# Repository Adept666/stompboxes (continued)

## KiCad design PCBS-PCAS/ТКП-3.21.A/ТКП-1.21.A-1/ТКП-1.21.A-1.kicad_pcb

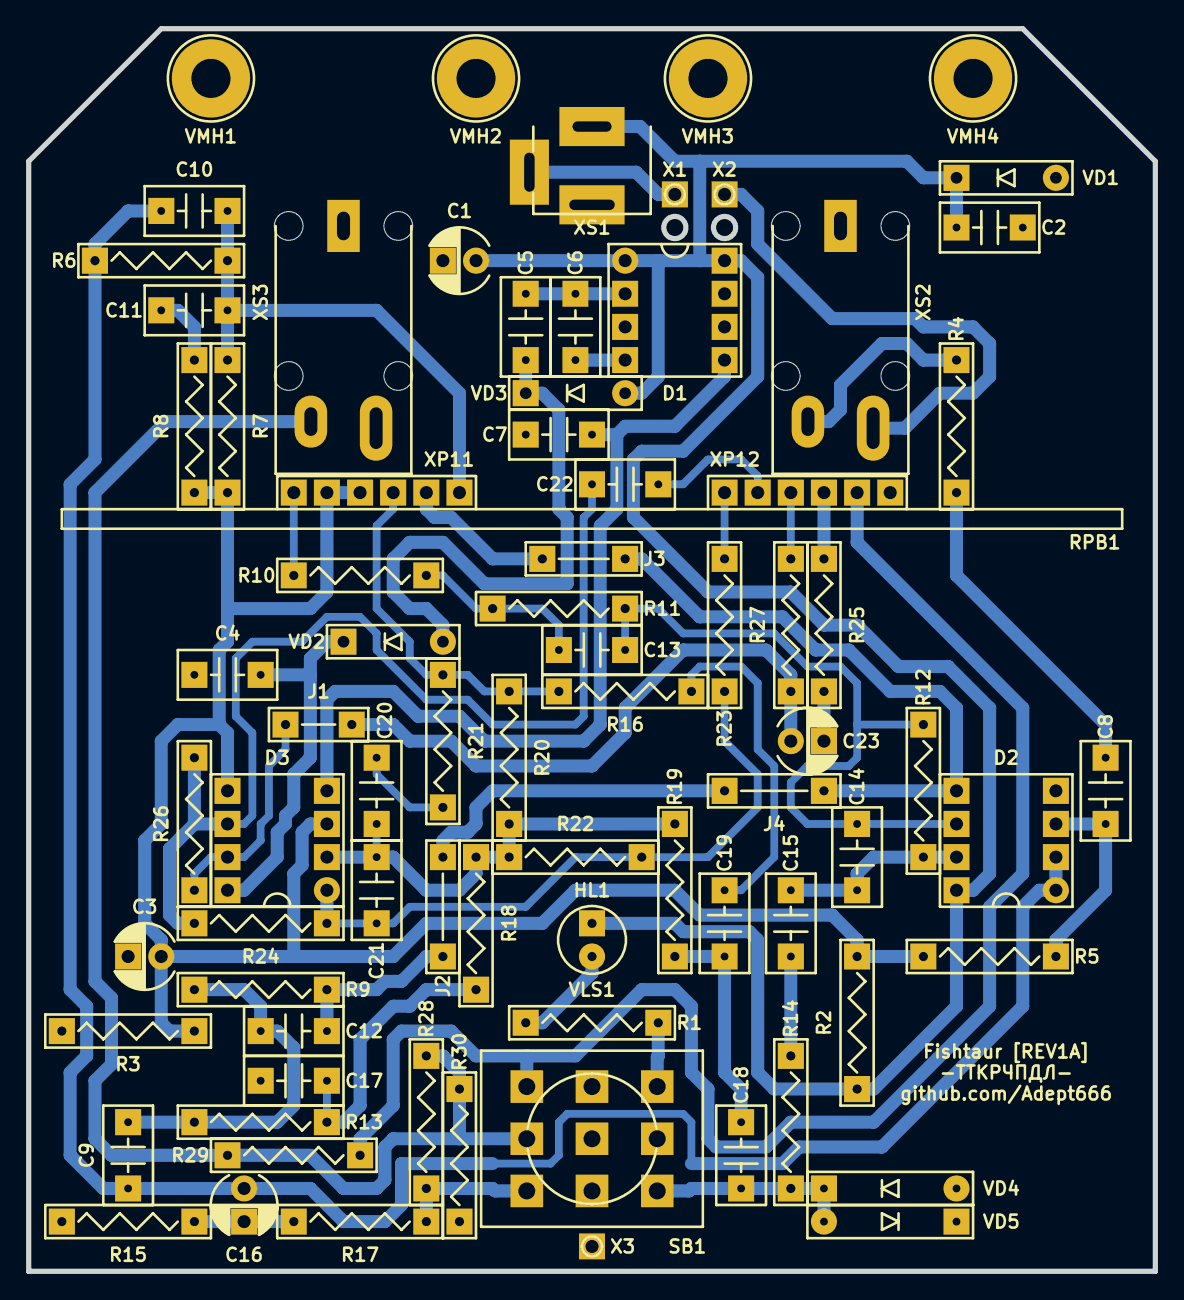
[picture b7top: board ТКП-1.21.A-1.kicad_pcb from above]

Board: 2 copper layers, 86.4 x 95.3 mm, 81 parts (0 on the bottom side), 44 nets.

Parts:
C1, C3: 476; CP-RADIAL-D05.0-P02.0-CLS
C2, C8, C9: 104; C-DISK-D04.2-T03.0-P05.08-d0.5
C4, C5, C6, C7, C15, C17, C18: 105; C-DISK-D04.2-T03.0-P05.08-d0.5
C10, C12: 683; C-DISK-D04.2-T03.0-P05.08-d0.5
C11: 334; C-DISK-D04.2-T03.0-P05.08-d0.5
C13: 823; C-DISK-D04.2-T03.0-P05.08-d0.5
C14: 391; C-DISK-D04.2-T03.0-P05.08-d0.5
C16, C23: 475; CP-RADIAL-D05.0-P02.0-CLS
C19: 222; C-DISK-D04.2-T03.0-P05.08-d0.5
C20: 223; C-DISK-D04.2-T03.0-P05.08-d0.5
C21: 821; C-DISK-D04.2-T03.0-P05.08-d0.5
C22: 392; C-DISK-D04.2-T03.0-P05.08-d0.5
D1: 7660S; P-DIP-08
D2, D3: 072; P-DIP-08
GB1: PP3; B-PP3-HV
HL1: FYL-5013UWC; LED-ROUND-05.0-UNI-SH-SPACER-PNL-5.3
J1: 0.6; J-TH-d0.6-P05.08
J2, J4: 0.6; J-TH-d0.6-P07.62
J3: 0.6; J-TH-d0.6-P06.35
R1, R4, R9: 103; R-MFR-25
R2, R3, R20: 273; R-MFR-25
R5: 105; R-MFR-25
R6: 512; R-MFR-25
R7, R13: 152; R-MFR-25
R8, R14: 102; R-MFR-25
R10: 202; R-MFR-25
R11, R18: 153; R-MFR-25
R12: 434; R-MFR-25
R15, R24, R26, R30: 104; R-MFR-25
R16: 223; R-MFR-25
R17, R25: 561; R-MFR-25
R19: 473; R-MFR-25
R21: 123; R-MFR-25
R22: 394; R-MFR-25
R23: 182; R-MFR-25
R27: 472; R-MFR-25
R28, R29: 683; R-MFR-25
RPB1: B100K-B10K-B10K; RPB-1590BB-18-3x17-DUAL-SINGLE-SINGLE-1.5-PNL-7.4-2.8
SB1: PBS-24-302SP; SW-PBS-24-302SP-2.5-PNL-13.0
VD1: 4742A; P-DO-41
VD2, VD3: 4001; P-DO-41
VD4, VD5: Д9Б; P-DO-7
VE1: 1590BB; 1590BB_B1
VLS1: BR-12.7; VLS-BR
VMH1, VMH2, VMH3, VMH4: DI5M3x18; VMH-STA-DA5-PNL-3.0
X1: +; CON-PAD-S-1.0-2.0
X2: -; CON-PAD-S-1.0-2.0
X3: COM; CON-PAD-S-1.0-2.0
XS1: DC-005; CON-DC-005
XS2: ST-008S-04; CON-ST-008X-04-OR-ST-008X-05
XS3: ST-008S-05; CON-ST-008X-04-OR-ST-008X-05

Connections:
/BYPASS: R17.2, R28.1, SB1.NC1
/EFFECT: R29.1, RPB1.32, SB1.NO1
/IN: R4.1, XS2.T
/J1: C23.+, D3.7, J1.J, R26.2, R27.2
/J2: C12.2, D2.5, J2.J, J3.J, J4.J, R9.2, RPB1.11
/LED: R1.1, SB1.NO3
/LED-CIR: C18.1, R14.2, SB1.NC3, VD4.C, VD5.A
/OUT: R28.2, R29.2, R30.2, SB1.COM1, XS3.T
/PP3-NEG: X2.1, XS2.R/TN
/PP3-POS: X1.1, XS1.SN
COM: C1.-, C2.2, C3.-, C4.2, C7.1, C17.2, D1.3, D2.4, R3.1, R15.1, R30.1, RPB1.31, SB1.COM2, SB1.COM3, SB1.NC2, VD1.A, VD4.A, VD5.C, VMH1.0, VMH2.0, VMH3.0, VMH4.0, X3.1, XS1.C, XS2.S, XS3.S
unnamed: C5.1, VD2.A, VD3.C
unnamed: C5.2, C6.1, D1.2
unnamed: C6.2, D1.4
unnamed: C8.1, R4.2
unnamed: C8.2, D2.3, R5.2
unnamed: C9.1, C10.1, C16.+, D2.1, D2.2, R6.2
unnamed: C10.2, C11.1, R6.1, R7.2, RPB1.14
unnamed: C11.2, R8.2
unnamed: C9.2, C12.1, R9.1, R13.1
unnamed: C13.1, R10.1, R11.1
unnamed: C13.2, C14.1, D2.6, R11.2, R12.1
unnamed: C14.2, C15.1, D2.7, R12.2
unnamed: C15.2, R14.1
unnamed: C16.-, R15.2, R17.1
unnamed: C17.1, R13.2, R18.1
unnamed: C18.2, C19.1, R19.1
unnamed: C19.2, R16.2
unnamed: C20.1, C21.1, D3.2, R18.2, R19.2, R20.2, R22.1
unnamed: C20.2, R21.2
unnamed: C21.2, D3.1, R22.2, R23.1, R24.1
unnamed: C22.1, RPB1.22
unnamed: C22.2, D3.6, R24.2, R26.1
unnamed: C23.-, R25.1
unnamed: HL1.C, R1.2
unnamed: R10.2, RPB1.13
unnamed: R16.1, R20.1, R21.1, RPB1.15
unnamed: R23.2, RPB1.23
unnamed: R25.2, RPB1.33
unnamed: R27.1, RPB1.21
VA: C1.+, C2.1, D1.1, D1.8, D2.8, HL1.A, R2.2, VD1.C, VD3.A, XS1.S
VB: C4.1, D3.8, VD2.C
VC: C7.2, D1.5, D3.4
VREF: C3.+, D3.3, D3.5, R2.1, R3.2, R5.1, R7.1, R8.1, RPB1.12, RPB1.16

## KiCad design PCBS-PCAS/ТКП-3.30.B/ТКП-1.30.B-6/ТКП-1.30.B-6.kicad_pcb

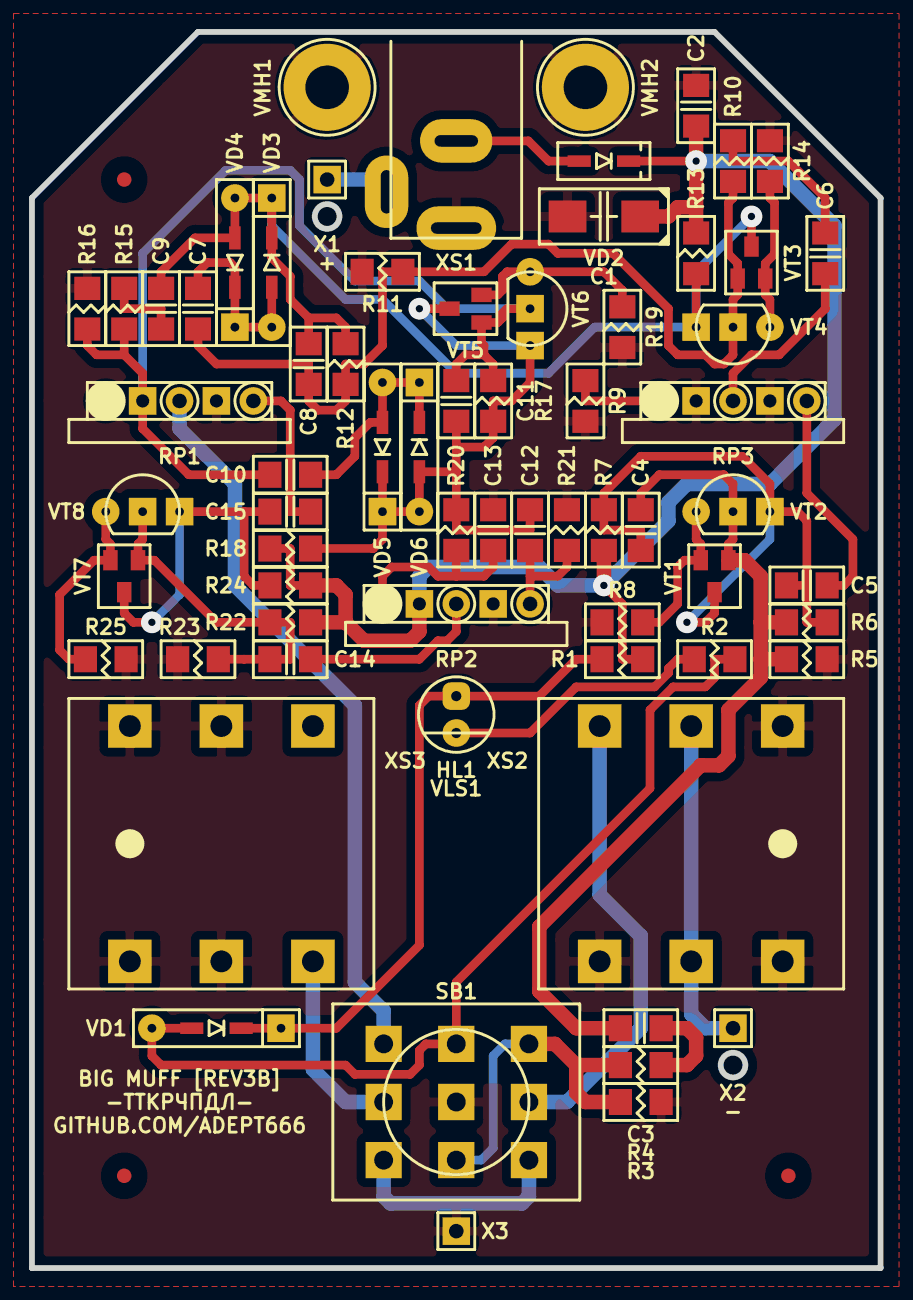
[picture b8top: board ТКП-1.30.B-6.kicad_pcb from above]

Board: 2 copper layers, 58.4 x 85.1 mm, 74 parts (0 on the bottom side), 37 nets.

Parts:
C1: 106; CP-CTSMD-C
C2, C5, C6, C9, C15: 104; C-SM-1206
C3, C14: 105; C-SM-1206
C4, C8, C11: 471; C-SM-1206
C7, C10: 683; C-SM-1206
C12: 332; C-SM-1206
C13: 103; C-SM-1206
GB1: X; B-PP3-HV
HL1: FYL-3014UWC; LED-ROUND-05.0-UNI-SH-SPACER-PNL-5.3
R1: 0; R-SM-1206
R2: 433; R-SM-1206
R3: 105; R-SM-1206
R4: 393; R-SM-1206
R5, R11, R16, R23: 104; R-SM-1206
R6, R12, R17, R22: 474; R-SM-1206
R7, R13, R18: 123; R-SM-1206
R8, R14, R19: 391; R-SM-1206
R9: 102; R-SM-1206
R10, R15, R24: 103; R-SM-1206
R20, R21: 223; R-SM-1206
R25: 272; R-SM-1206
RP1, RP3: A100K; RPB-18-1x17-1.6-PNL-7.2
RP2: B100K; RPB-18-1x17-1.6-PNL-7.2
SB1: PBS-24-302SP; SW-PBS-24-302SP-2.5-PNL-12.0
VD1: X; P-SOD-123-OR-DO-35-V2
VD2: 0520; P-SOD-123
VD3, VD4, VD5, VD6: 4148; P-SOD-123-OR-DO-35-V2
VE1: ТКП-6.3.1.A2.A1.A.1-1; ТКП-6.3.1.A2.A1.A
VE2: ТКП-6.3.3.A1.A1.3-1.A1.00; ТКП-6.3.3.A1
VFM1, VFM2, VFM3: 1.0; VFM-1.0-3.0-SL
VLS1: 2xBR-7.7; VLS-BR-P
VMH1, VMH2: DI5M3x20; VMH-STA-DA5-PNL-3.0
VT1, VT3, VT5, VT7: 847; P-SOT-23-B-E-C
VT2, VT4, VT6, VT8: 547; P-TO-92-E-B-C
X1, X2, X3: X; CON-PAD-S-1.0-1.9
XS1: DC-005; CON-DC-005-9V-OVAL
XS2, XS3: PJ-644C; CON-PJ-644C-IN-OR-OUT

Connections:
/1B: C3.2, C4.1, R5.2, R6.1, VT1.B, VT2.B
/1C: C4.2, C5.1, R6.2, R7.1, VT1.C, VT2.C
/1E: R8.2, VT1.E, VT2.E
/2B: C7.1, C8.1, R10.2, R11.2, R12.1, VT3.B, VT4.B
/2C: C8.2, C9.1, R12.2, R13.1, VD3.C, VD4.A, VT3.C, VT4.C
/2E: R14.2, VT3.E, VT4.E
/3B: C10.1, C11.1, R15.2, R16.2, R17.1, RP1.NC1, VT5.B, VT6.B
/3C: C11.2, C12.1, R17.2, R18.1, R20.1, VD5.C, VD6.A, VT5.C, VT6.C
/3E: R19.2, VT5.E, VT6.E
/4B: C14.2, R22.1, R23.2, VT7.B, VT8.B
/4C: C15.1, R24.1, VT7.C, VT8.C
/4E: R25.2, VT7.E, VT8.E
/IN-CIR: R3.2, R4.1, SB1.NC2, SB1.NO3
/IN-CON: SB1.COM3, XS2.T
/LED: R2.1, SB1.NO2, VD1.A
/OUT-CIR: RP1.2, SB1.NO1
/OUT-CON: SB1.COM1, XS3.T
/PP3-NEG: X2.1, XS2.R, XS2.RN
/PP3-POS: X1.1, XS1.SN
COM: C1.-, C2.2, C13.2, R3.1, R5.1, R8.1, R9.1, R11.1, R14.1, R16.1, R19.1, R21.2, R23.1, R25.1, RP1.1, RP1.NC2, RP2.NC2, RP3.NC1, RP3.NC2, SB1.COM2, VMH1.0, VMH2.0, X3.1, XS1.C, XS2.S, XS2.SN, XS2.TN, XS3.R, XS3.RN, XS3.S, XS3.SN
unnamed: C3.1, R4.2
unnamed: C5.2, RP3.3
unnamed: C6.1, RP3.2
unnamed: C6.2, R10.1
unnamed: C7.2, VD3.A, VD4.C
unnamed: C9.2, R15.1
unnamed: C10.2, VD5.A, VD6.C
unnamed: C12.2, R21.1, RP2.3
unnamed: C13.1, R20.2, RP2.1
unnamed: C14.1, RP2.2
unnamed: C15.2, RP1.3
unnamed: HL1.A, R1.2, VD1.C
unnamed: HL1.C, R2.2
unnamed: R9.2, RP3.1
unnamed: SB1.NC1, SB1.NC3
unnamed: VD2.A, XS1.S
V: C1.+, C2.1, R1.1, R7.2, R13.2, R18.2, R22.2, R24.2, RP2.NC1, VD2.C

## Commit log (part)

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2023-08-25 ТКП-1.23.A-1 Salty Phaser [REV1A]: minor changes
2023-08-25 ТКП-1.37.A Little Angel Chorus [REV2A]: project files are moved to cipher-based storage directory
2023-08-25 Minor changes
2023-09-18 Enclosure parts: ТКП-6.3.2.A1 added
2023-09-19 Enclosure parts: ТКП-6.3.1.A1 modified
2023-09-24 Enclosure parts: draft version of ТКП-6.3.3.A1 added
2023-09-24 Enclosure parts: ТКП-6.3.1.B1 modified
2023-09-24 Enclosure parts: minor changes
2023-10-07 SBKCL: CP-RADIAL-D05.0-P02.0-CLS-OR-D06.3-P02.5-CLS-OR-D08.0-P03.5-CLS footprints modified
2023-10-07 ТКП-1.23.B-1 Salty Phaser [REV1B]: technical requirements added
2023-10-07 ТКП-1.23.B-1 Salty Phaser [REV1B]: TP4…7 added
2023-10-08 ТКП-1.23.B-1 Salty Phaser [REV1B]: PS.VD2 added
2023-10-08 ТКП-1.23.B-1 Salty Phaser [REV1B]: J1, J2, TP8, and TP9 added
2023-10-08 ТКП-1.23.B-1 Salty Phaser [REV1B]: L.R9 added
2023-10-08 ТКП-1.23.B-1 Salty Phaser [REV1B]: L.R10 added
2023-10-09 ТКП-1.23.B-1 Salty Phaser [REV1B]: J6, J7, and L.J1 added
2023-10-15 ТКП-1.23.B-1 Salty Phaser [REV1B]: PS.C6, PS.D1, PS.R3, PS.R4, PS.VD3, and PS.VD4 added
2023-10-25 ТКП-1.23.B-1 Salty Phaser [REV1B]: MS.R9 and MS.R10 added
2023-10-29 ТКП-1.23.B-1 Salty Phaser [REV1B]: TP11 added
2023-10-30 ТКП-1.38.A Phaser A [REV1A]: some changes
2023-10-30 ТКП-1.27.B 1590N1 Connector Board [REV1B]: project files are moved to cipher-based storage directory
2023-11-07 ТКП-1.27.B-1 1590N1 Connector Board [REV1B] A: minor changes
2023-11-13 ТКП-1.23.B-1 Salty Phaser [REV1B]: VLS1…4 footprints changed
2023-11-13 ТКП-1.27.B-1 1590N1 Connector Board [REV1B] A: output files updated
2023-11-14 ТКП-1.27.B-3 1590N1 Connector Board [REV1B] C files added
2023-11-18 SBKCL: minor changes
2023-11-23 Big Muff [REV3SM]: some engraving files added
2023-11-26 Enclosure parts: ТКП-6.1.1.B1 added
2023-12-09 ТКП-1.20.B 1590BB Potentiometer Board 18 3x17 [REV1B]: project files are moved to cipher-based storage directory
2023-12-09 ТКП-1.26.C 1590N1 Potentiometer Board 18 2x17 [REV1C]: project files are moved to cipher-based storage directory
2023-12-17 ТКП-1.39.A-1 Salty Phaser Potentiometer Board [REV2A] files added
2023-12-18 ТКП-3.42.A Spacer PJ-644C [REV1A] files added
2023-12-19 ТКП-3.36.A Spacer MTS-1xx-A2 [REV1A]: project files are moved to cipher-based storage directory
2023-12-19 ТКП-1.35.A-1 Тремоло Саши Огородникова Potentiometer Board [REV2A]: some changes
2023-12-20 ТКП-1.29.A-1 Edamamer Potentiometer Board [REV1A]: some changes
2023-12-20 ТКП-1.23.B-1 Salty Phaser [REV1B]: VE1 changed from ТКП-6.1.1.A1-2 to ТКП-6.1.1.B1-1, other minor changes
2023-12-23 Enclosure parts: ТКП-6.1.5.A1 added
2023-12-23 Salty Phaser [REV1SM]: draft engraving file added
2024-01-07 ТКП-1.23.B-1 Salty Phaser [REV1B]: X1 changed to X
2024-01-13 ТКП-1.27.A-1 1590N1 Connector Board [REV1A] A: minor changes
2024-01-13 ТКП-1.27.A-1 1590N1 Connector Board [REV1A] A: output files updated
2024-01-14 ТКП-1.34.A 1590BB2 Connector Board Extended [REV1A]: project files are moved to cipher-based storage directory
2024-01-14 ТКП-1.34.A-1 1590BB2 Connector Board Extended [REV1A] A: some changes, technical requirements added, output files updated
2024-01-16 ТКП-3.41.A 1590BB Potentiometer Board 18 3x17 [REV2A]: gerbers added
2024-01-19 ТКП-1.30.A Big Muff [REV3A]: project files are moved to cipher-based storage directory
2024-01-21 ТКП-1.30.A Big Muff [REV3A]: output files updated
2024-01-29 ТКП-1.30.A-3 and ТКП-1.30.A-4 files added
2024-01-31 ТКП-1.30.A-3 and ТКП-1.30.A-4: VE1 changed, VE2 added, washers removed, remaining output files added
2024-02-04 Fuzz Factory [REV1SM]: some engraving files added
2024-02-06 Fuzz Factory [REV1SM]: remaining engraving files added
2024-02-07 Salty Phaser [REV1SM]: some draft engraving files added
2024-02-15 Fuzz Factory [REV1SM]: some engraving files modified
2024-03-02 Enclosure parts: ТКП-6.4.2.A1.A1 added
2024-03-02 ТКП-1.39.A-1 Salty Phaser Potentiometer Board [REV2A]: some changes, remaining output files added
2024-04-29 ТКП-1.31.A Potentiometer Board 18 1x17 [REV1A]: project files are moved to cipher-based storage directory
2024-04-29 ТКП-1.31.A-3 Potentiometer Board 18 1x17 [REV1A] R16K1-20F-B50K files added
2024-05-11 SBEL: ТКП-6.4.1.A1 added
2024-05-19 ТКП-1.18.A-2 Potentiometer Board 20 1x17 [REV1A] R16K1-20F-B50K Trimmed files added
2024-05-20 ТКП-1.13.A Big Muff [REV2A]: minor changes
2024-05-25 ТКП-1.11.A-1 Distortion + [REV2A]: project files are moved to cipher-based storage directory
2024-05-26 ТКП-1.11.A-1 Distortion + [REV2A]: minor changes, output files updated
2024-06-02 Enclosure parts: ТКП-6.1.5.B1 added
2024-06-02 SBEL: ТКП-6.1.5.B1 and ТКП-6.1.5.C1 added
2024-06-08 ТКП-1.19.B-1 Good Grief Overdrive [REV1B]: minor changes
2024-06-08 ТКП-1.19.B-2 Good Grief Overdrive [REV1B] SM: VLS1 changed from BR-17.8 to BR-12.7
2024-06-09 ТКП-1.19.A-1 Good Grief Overdrive [REV1A]: minor changes, output files updated
2024-06-15 ТКП-1.39.A-3 Копка Земли Potentiometer Board [REV2A] files added
2024-06-16 ТКП-1.12.A-1 Little Angel Chorus [REV1A]: minor changes, output files updated
2024-06-19 ТКП-1.24.A Копка Земли [REV1A]: minor changes
2024-06-21 Fuzz Factory [MB:REV1C/PB:REV1B]: minor changes
2024-06-27 SBKCL-TH-ML: RPB-20-1x17-1.6-PNL-7.4-2.8 footprint added
2024-07-07 ТКП-1.17.C-1 Deep Blue Delay [REV3C] files added
2024-07-21 ТКП-1.17.B-1 Deep Blue Delay [REV3B]: VE1 changed from B013_D1 to B013_E1, VLS1 changed from BR-17.8 to BR-12.7, VMH1 and VMH2 changed from DI5M3x20 to DI5M3x18, screws DIN 965 changed to DIN 7985
2024-07-27 ТКП-1.30.A-3 and ТКП-1.30.A-4: spacer ТКП-3.35.A removed, other minor changes
2024-08-04 Копка Земли [REV2SM] Down-Tuned: some engraving files added
2024-08-07 ТКП-3.30.B Big Muff [REV3B]: gerbers added
2024-08-09 ТКП-3.43.A Spacer PBS-24-302SP [REV2A] files added
2024-08-11 Enclosure parts: ТКП-6.1.5.D1 added
2024-08-24 ТКП-1.28.A-1 Edamamer [REV1A]: minor changes
2024-08-31 Fuzz Factory [MB:REV1D/PB:REV1C]: project files are moved to cipher-based storage directory
2024-09-01 Fuzz Factory [MB:REV1D/PB:REV1C]: minor changes, output files updated
2024-09-01 Fuzz Factory [MB:REV1C/PB:REV1B]: minor changes, output files updated
2024-09-01 Fuzz Factory [MB:REV1B/PB:REV1B]: minor changes
2024-09-04 Fuzz Factory [MB:REV1B/PB:REV1B]: minor changes, output files updated
2024-09-14 ТКП-3.35.A Spacer PBS-24-302SP [REV1A]: minor changes
2024-09-14 ТКП-3.36.A Spacer MTS-1xx-A2 [REV1A]: minor changes
2024-10-09 ТКП-1.22.B-1 Fishtaur Potentiometer Board [REV1B]: project files are moved to cipher-based storage directory
2024-10-09 ТКП-1.22.B-1 Fishtaur Potentiometer Board [REV1B]: minor changes
2024-10-09 ТКП-1.22.B-1 Fishtaur Potentiometer Board [REV1B]: minor changes, output files updated
2024-11-25 StompBoxes' Enclosure Part Library (SBEPL) created
2024-11-29 ТКП-1.36.A-3 and ТКП-1.36.A-4 files added
2024-11-30 ТКП-1.36.A-3 and ТКП-1.36.A-4: some output files added
2024-12-01 ТКП-1.36.A-3 and ТКП-1.36.A-4: some changes, remaining output files added
2024-12-06 ТКП-1.17.C-2 Deep Blue Delay [REV3C] SM files added
2024-12-08 SBEL: ТКП-6.1.1, ТКП-6.1.3, and ТКП-6.1.5 parts moved to SBEPL
2024-12-12 ТКП-1.32.A-1 Crumbwave Multiplexer [REV1A]: project files are moved to cipher-based storage directory
2024-12-14 ТКП-1.32.A-1 Crumbwave Multiplexer [REV1A]: output files updated
2024-12-14 ТКП-1.25.B-1 Тремоло Саши Огородникова [REV1B]: minor changes
2024-12-15 ТКП-1.25.A-1 Тремоло Саши Огородникова [REV1A]: project files are moved to cipher-based storage directory
2024-12-15 ТКП-1.25.A-1 Тремоло Саши Огородникова [REV1A]: jumpers VJ1…4 and trace cuts VTC1…5 added
2024-12-16 ТКП-1.25.A-1 Тремоло Саши Огородникова [REV1A]: some changes
2024-12-17 ТКП-1.25.A-1 Тремоло Саши Огородникова [REV1A]: remaining output files added
2024-12-18 ТКП-1.26.A-1 Тремоло Саши Огородникова Potentiometer Board [REV1A]: some changes, output files updated
2024-12-29 ТКП-1.35.A-1 Тремоло Саши Огородникова Potentiometer Board [REV2A]: RP1 and RP2 replaced from R16K1-L20KC with PDB181-K420K
2024-12-30 ТКП-1.30.A-3 Big Muff [REV3A] NYC SM: RP1…3 replaced from R16K1-L20KC with PDB181-K420K, VE1 replaced from ТКП-6.3.1.A1-1 with ТКП-6.3.1.A2.A1.A.1-1, VE2 cipher changed from ТКП-6.3.3.A1-1 to ТКП-6.3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
2024-12-31 ТКП-1.23.B-1 Salty Phaser [REV1B]: VE1 cipher changed from ТКП-6.1.1.B1-1 to ТКП-6.1.1.A1.B1.A.1-1, VE2 cipher changed from ТКП-6.1.5.A1-1 to ТКП-6.1.3.A2.D1.2-1.D1.E1
2025-01-02 ТКП-1.19.B-2 Good Grief Overdrive [REV1B] SM: D1 replaced from LM833N with RC4558P, R10 and R11 tolerance changed from 5% to 1%
2025-01-02 ТКП-1.24.B-3 Копка Земли [REV1B] Down-Tuned SM: VE1 cipher changed from ТКП-6.1.1.A1-2 to ТКП-6.1.1.A1.A1.A.1-1, VE2 cipher changed from ТКП-6.1.5.C1-1 to ТКП-6.1.3.A2.C1.2-1.B2.C1
2025-01-03 ТКП-1.21.A-2 Fishtaur [REV1A] SM: VE1 cipher changed from ТКП-6.1.1.A1-2 to ТКП-6.1.1.A1.A1.A.1-1, VE2 cipher changed from ТКП-6.1.3.B1-1 to ТКП-6.1.3.A1.B1.2-1.A1.B1
2025-01-04 ТКП-1.23.A-1 Salty Phaser [REV1A]: VE2 cipher changed from ТКП-6.1.4.A1-1 to ТКП-6.1.4.A1.A1.2-1.A1, XS2 and XS3 replaced from PJ-309 with ST-008S-05/04
2025-01-05 Graphic layouts storage method transformed (in progress)
2025-01-08 Great Depression Phaser [REV1SM]: some engraving files added
2025-01-24 Great Depression Phaser [REV1SM]: remaining engraving files added
2025-01-25 Great Depression Phaser [REV1]: some UV-printing files added
2025-01-27 ТКП-1.26.B-2 Great Depression Phaser Potentiometer Board [REV1B] files added
2025-02-19 Great Depression Phaser [REV1SM]: engraving files updated
2025-05-04 ТКП-1.38.A-2 Great Depression Phaser [REV1A] SM files added
2025-05-05 ТКП-1.30.B-4 Big Muff [REV3B] Bass SM files added
2025-05-08 ТКП-1.37.A-1 Little Angel Chorus [REV2A]: DWS.R1 and L.R6 values changed from X to 0, RPB1.1 and RPB1.2 replaced from R16K1-L15KC B50K to RV16AF-20-15K C50K
2025-06-04 Deep Blue Delay [REV3SM]: some engraving files added
2025-06-07 Big Muff [REV3SM] Bass: remaining engraving files added
2025-06-12 ТКП-1.31.A-7 and ТКП-1.31.A-8 files added
2025-06-12 ТКП-1.35.A-3 Little Angel Chorus Potentiometer Board [REV2A] files added
2025-06-17 ТКП-1.17.C-2 Deep Blue Delay [REV3C] SM: VE2 cipher changed from ТКП-6.3.3.A1.A1.2-1.A1.00 to ТКП-6.3.3.A1.A1.3-1.A1.00
2025-06-19 ТКП-1.30.B-3 and ТКП-1.30.B-4: VE2 cipher changed from ТКП-6.3.3.A1.A1.2-1.A1.00 to ТКП-6.3.3.A1.A1.3-1.A1.00
2025-06-21 ТКП-1.30.B-1 Big Muff [REV3B] NYC: some changes, output files added
2025-06-21 ТКП-1.30.A-5 and ТКП-1.30.A-6 files added
2025-06-21 SBEPL: Minor changes
2025-06-24 ТКП-1.21.A-3 Fishtaur [REV1A] SM LC5-8 files added
2025-08-09 SBEPL: ТКП-6.2.1.A1.A1.A added
2025-08-10 ТКП-1.17.C-3 Deep Blue Delay [REV3C] SM LC5-8 files added
2025-11-02 ТКП-1.21.A-2 Fishtaur [REV1A] SM: top screws replaced from DIN 7985 with DIN 7380-1, washers removed
2025-11-04 ТКП-1.17.B-2 Deep Blue Delay [REV3B] SM: top screws replaced from DIN 7985 with DIN 7380-1
2025-11-04 ТКП-1.17.C-3 Deep Blue Delay [REV3C] SM LC5-8: top screws replaced from DIN 7985 with DIN 7380-1
2025-11-07 ТКП-1.31.A-9 Potentiometer Board 18 1x17 [REV1A] R16K1-15KC-B50K files added
2025-11-09 ТКП-1.30.A-3 Big Muff [REV3A] NYC SM: top screws replaced from DIN 7985 with DIN 7380-1
2025-11-09 ТКП-1.30.B-3 Big Muff [REV3B] NYC SM: top screws replaced from DIN 7985 with DIN 7380-1
2025-11-15 ТКП-1.30.A-5 Big Muff [REV3A] NYC SM LC5-8: top screws replaced from DIN 7985 with DIN 7380-1
2025-11-15 ТКП-1.30.B-5 Big Muff [REV3B] NYC SM LC5-8: top screws replaced from DIN 7985 with DIN 7380-1
2026-05-03 ТКП-1.12.A-1 Little Angel Chorus [REV1A]: some changes
2026-05-27 ТКП-1.36.A-5 Копка Земли [REV2A] Down-Tuned SM LC5-8 files added
2026-06-07 SBKCL-TH-ML: RPB-18-1x17-1.6 footprint added
